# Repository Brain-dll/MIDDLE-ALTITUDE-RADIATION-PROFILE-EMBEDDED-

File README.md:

# Radiation-Profile-of-3000
Radiation profile of middle altitude rocket's route will be created at this project as payload mission

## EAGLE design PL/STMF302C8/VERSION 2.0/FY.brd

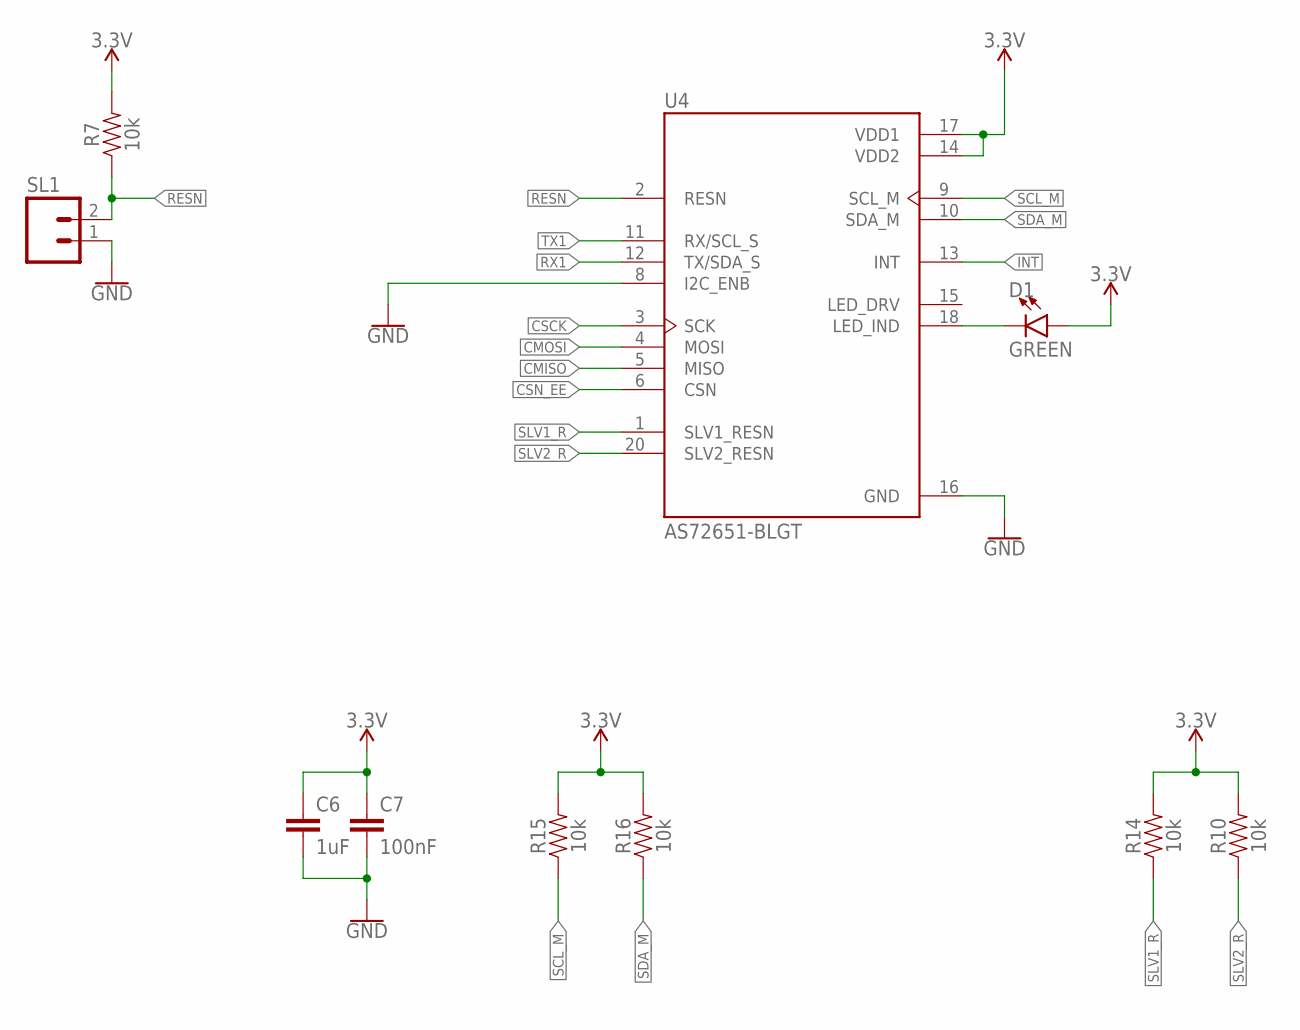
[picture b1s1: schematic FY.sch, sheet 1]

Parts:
C6: 1uF; 0603
C7: 100nF; 0603
D1: GREEN; LED-0603
R7, R10, R14, R15, R16: 10k; 0603
SL1: M02; 02P
U4: AS72651-BLGT; PQFN65P470X450X270-20N

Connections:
3.3V: C6.1, C7.1, D1.A, R7.2, R10.2, R14.2, R15.2, R16.2, U4.14 (VDD2), U4.17 (VDD1); also elsewhere on the board
CMISO: U4.5 (MISO); also elsewhere on the board
CMOSI: U4.4 (MOSI); also elsewhere on the board
CSCK: U4.3 (SCK); also elsewhere on the board
CSN_EE: U4.6 (CSN); also elsewhere on the board
GND: C6.2, C7.2, SL1.1, U4.8 (I2C_ENB), U4.16 (GND); also elsewhere on the board
INT: U4.13 (INT); also elsewhere on the board
unnamed: D1.C, U4.18 (LED_IND)
RESN: R7.1, SL1.2, U4.2 (RESN)
RX1: U4.12 (TX/SDA_S); also elsewhere on the board
SCL_M: R15.1, U4.9 (SCL_M); also elsewhere on the board
SDA_M: R16.1, U4.10 (SDA_M); also elsewhere on the board
SLV1_R: R14.1, U4.1 (SLV1_RESN); also elsewhere on the board
SLV2_R: R10.1, U4.20 (SLV2_RESN); also elsewhere on the board
TX1: U4.11 (RX/SCL_S); also elsewhere on the board

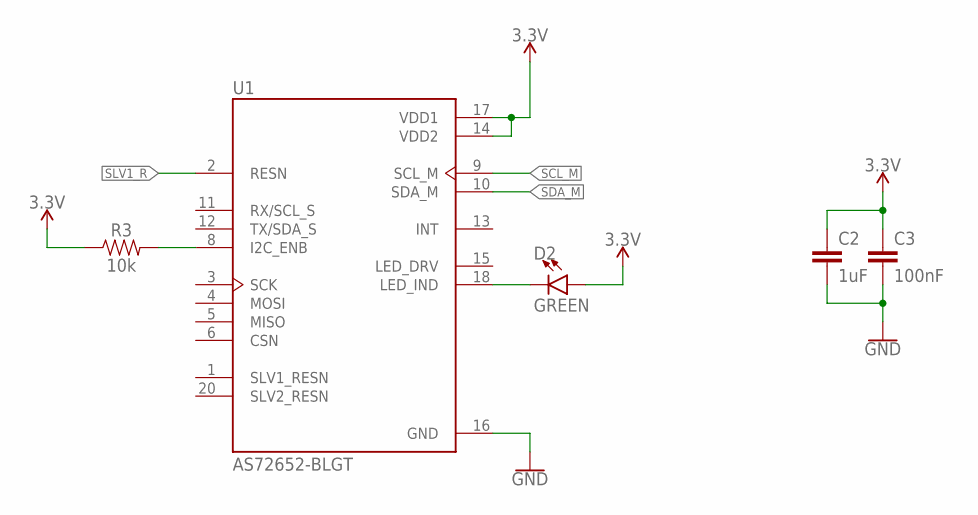
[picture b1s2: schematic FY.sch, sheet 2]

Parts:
C2: 1uF; 0603
C3: 100nF; 0603
D2: GREEN; LED-0603
R3: 10k; 0603
U1: AS72652-BLGT; PQFN65P470X450X270-20N

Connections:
3.3V: C2.1, C3.1, D2.A, R3.1, U1.14 (VDD2), U1.17 (VDD1); also elsewhere on the board
GND: C2.2, C3.2, U1.16 (GND); also elsewhere on the board
unnamed: R3.2, U1.8 (I2C_ENB)
unnamed: D2.C, U1.18 (LED_IND)
SCL_M: U1.9 (SCL_M); also elsewhere on the board
SDA_M: U1.10 (SDA_M); also elsewhere on the board
SLV1_R: U1.2 (RESN); also elsewhere on the board

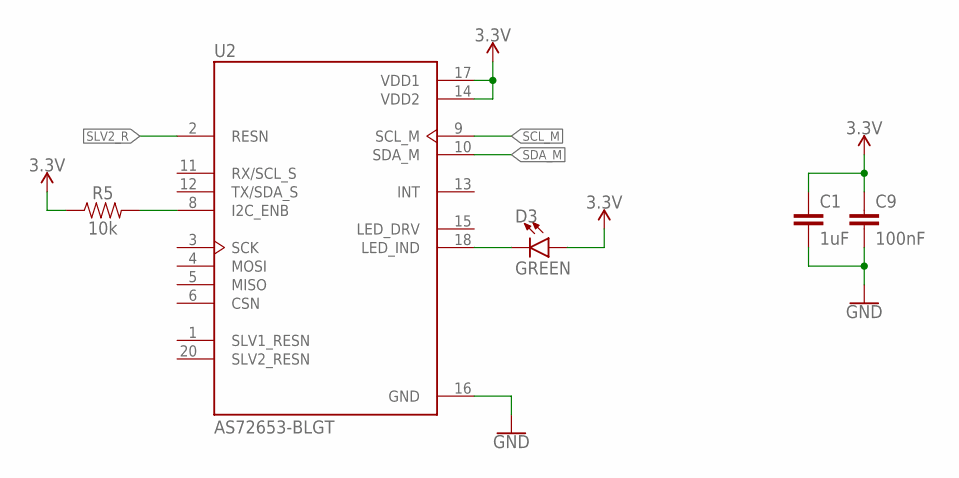
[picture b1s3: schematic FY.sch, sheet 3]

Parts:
C1: 1uF; 0603
C9: 100nF; 0603
D3: GREEN; LED-0603
R5: 10k; 0603
U2: AS72653-BLGT; PQFN65P470X450X270-20N

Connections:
3.3V: C1.1, C9.1, D3.A, R5.1, U2.14 (VDD2), U2.17 (VDD1); also elsewhere on the board
GND: C1.2, C9.2, U2.16 (GND); also elsewhere on the board
unnamed: D3.C, U2.18 (LED_IND)
unnamed: R5.2, U2.8 (I2C_ENB)
SCL_M: U2.9 (SCL_M); also elsewhere on the board
SDA_M: U2.10 (SDA_M); also elsewhere on the board
SLV2_R: U2.2 (RESN); also elsewhere on the board

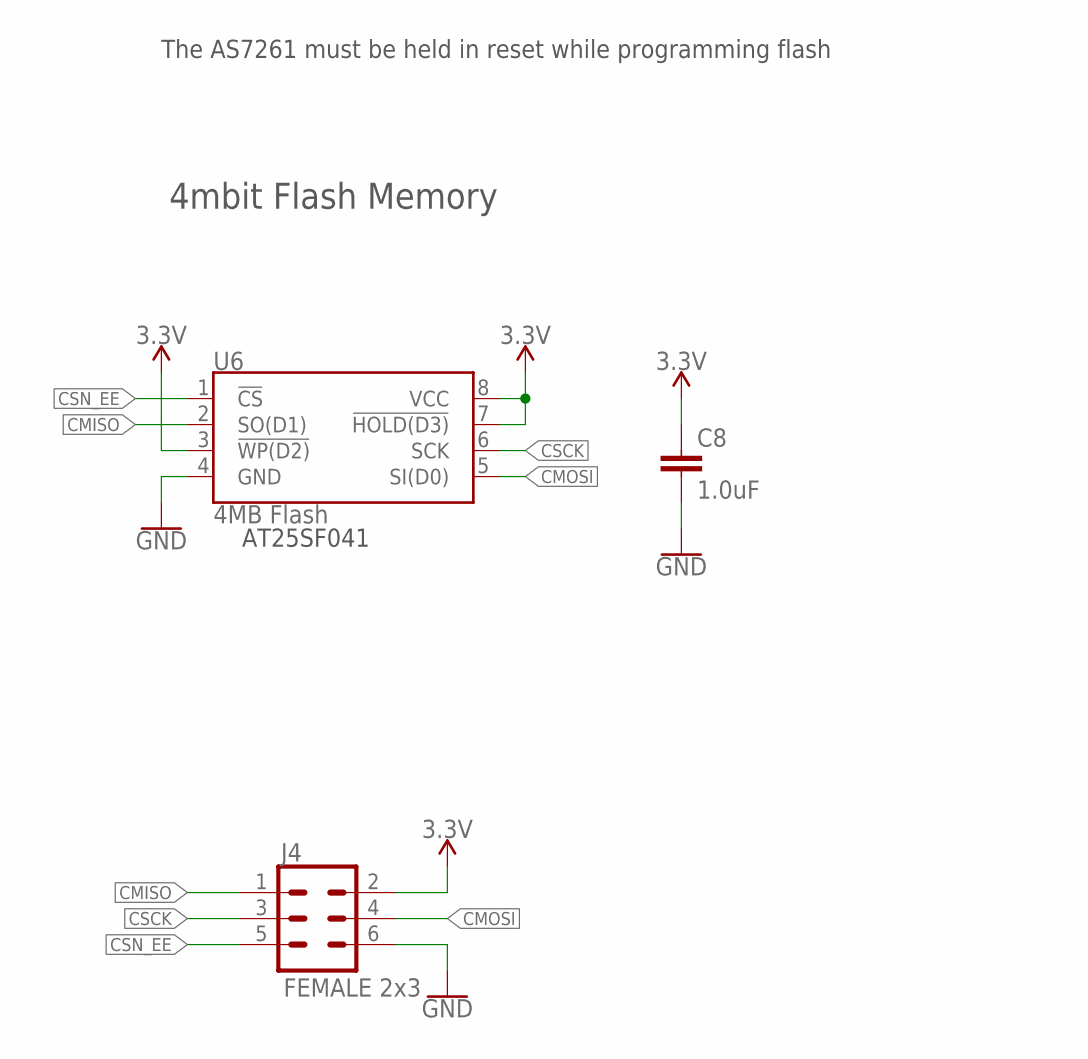
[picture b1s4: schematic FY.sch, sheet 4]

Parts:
C8: 1.0uF; 0603
J4: FEMALE 2x3; 2X3
U6: 4MB Flash; SO08

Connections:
3.3V: C8.1, J4.2, U6.3 (!WP(D2)), U6.7 (!HOLD(D3)), U6.8 (VCC); also elsewhere on the board
CMISO: J4.1, U6.2 (SO(D1)); also elsewhere on the board
CMOSI: J4.4, U6.5 (SI(D0)); also elsewhere on the board
CSCK: J4.3, U6.6 (SCK); also elsewhere on the board
CSN_EE: J4.5, U6.1 (!CS); also elsewhere on the board
GND: C8.2, J4.6, U6.4 (GND); also elsewhere on the board

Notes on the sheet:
4mbit Flash Memory
The AS7261 must be held in reset while programming flash
AT25SF041

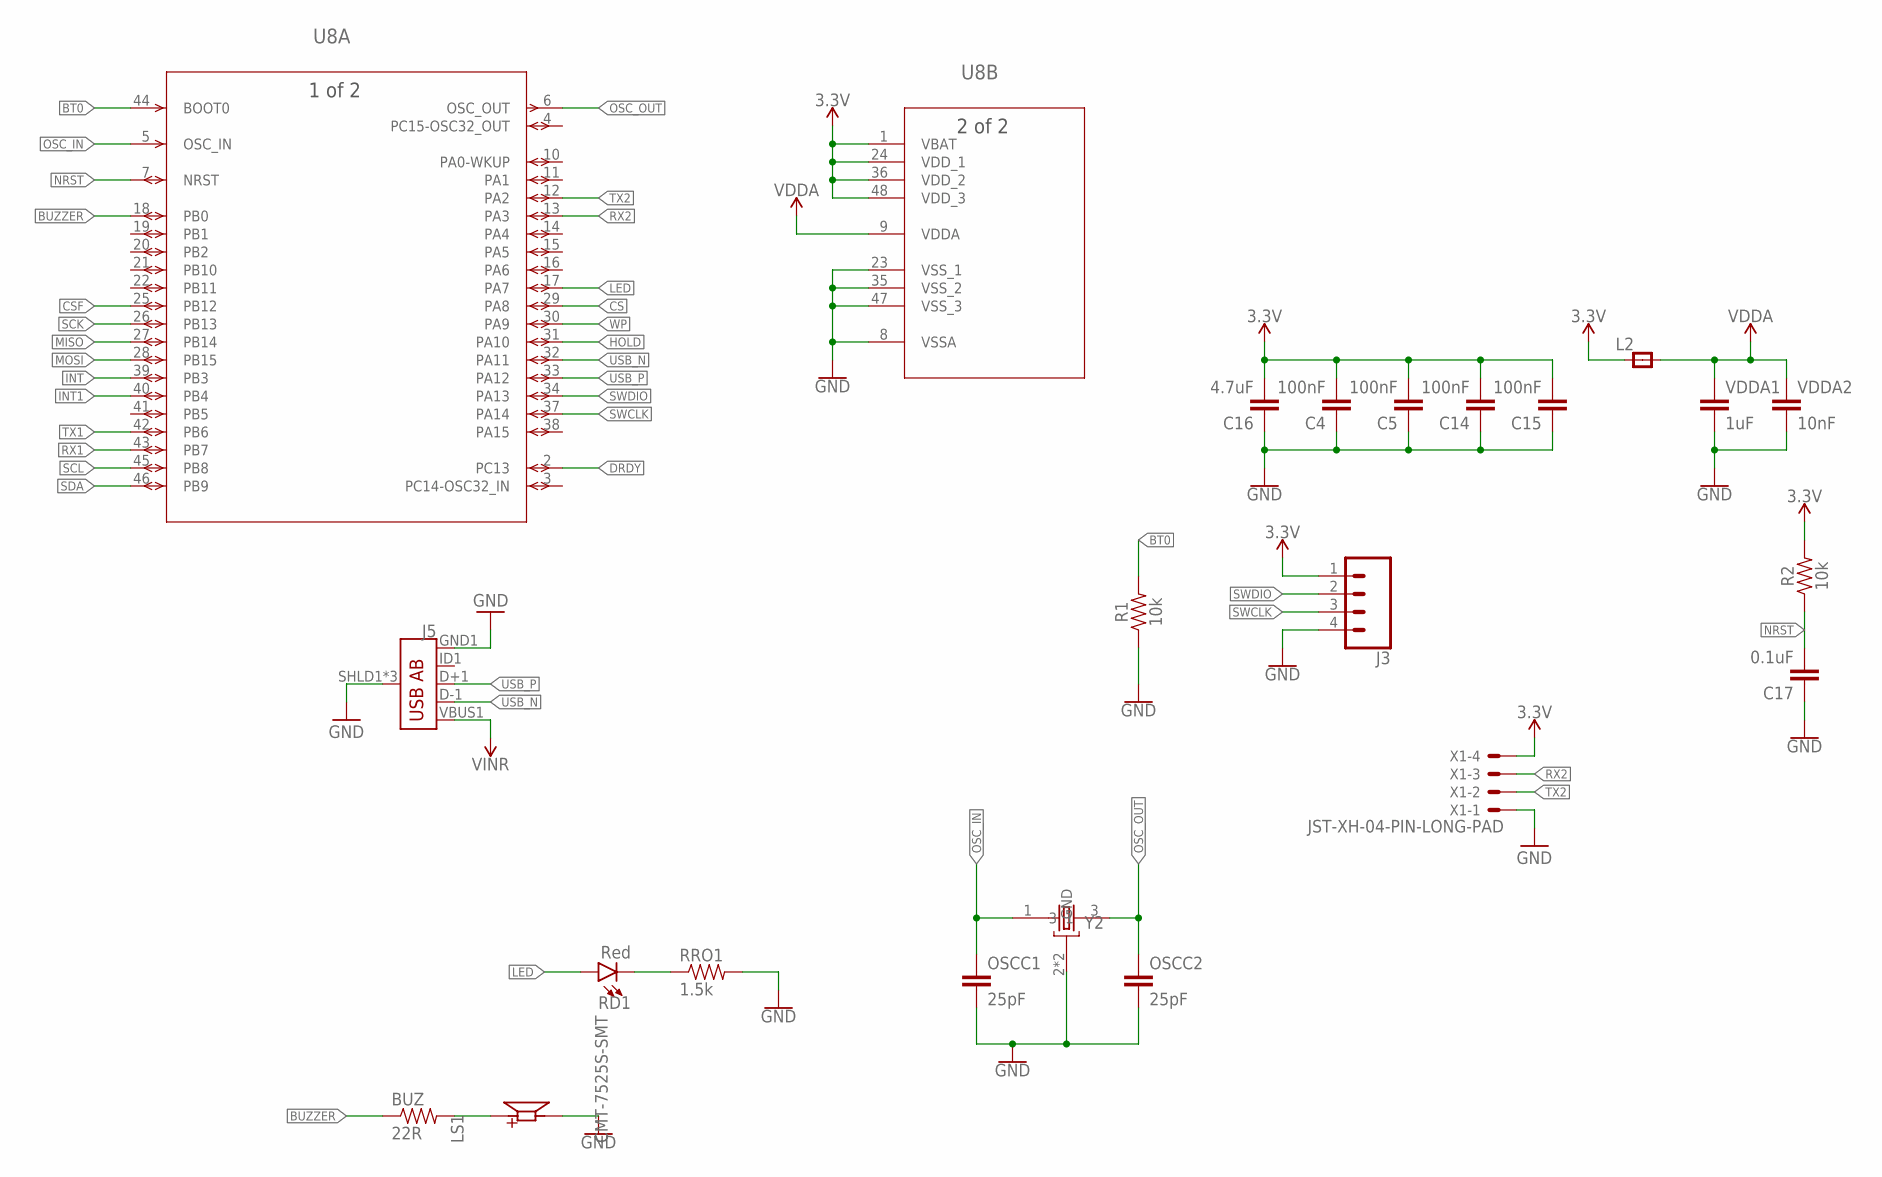
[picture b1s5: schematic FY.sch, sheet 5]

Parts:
BUZ: 22R; 0603-RES
C4, C5, C14, C15: 100nF; 0603
C16: 4.7uF; 0603
C17: 0.1uF; 0603
J3: CONN_04; 1X04
J5: USB_AB_SMT; USB-AB-MICRO-SMD
L2: RC-MASTER-SMD_FB_0805MP; RC-MASTER-SMD_L0805MP
LS1: CMT-7525S-SMT; CUI_CMT-7525S-SMT
OSCC1, OSCC2: 25pF; 0603
R1, R2: 10k; 0603
RD1: Red; LED-0603
RRO1: 1.5k; 0603-RES
U8: STM32F103C8T6; LQFP48-7X7MM
VDDA1: 1uF; 0603
VDDA2: 10nF; 0603
X1: JST-XH-04-PIN-LONG-PAD; JST-XH-04-PACKAGE-LONG-PAD
Y2: ABM2B-8.000MHZ-10-1-U-T; OSCCC500X320X110-4N

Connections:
3.3V: C4.2, C5.2, C14.2, C15.2, C16.2, J3.1, L2.1, R2.2, U8.1 (VBAT), U8.24 (VDD_1), U8.36 (VDD_2), U8.48 (VDD_3), X1.4; also elsewhere on the board
BT0: R1.2, U8.44 (BOOT0)
BUZZER: BUZ.1, U8.18 (PB0)
CS: U8.29 (PA8); also elsewhere on the board
CSF: U8.25 (PB12); also elsewhere on the board
DRDY: U8.2 (PC13); also elsewhere on the board
GND: C4.1, C5.1, C14.1, C15.1, C16.1, C17.1, J3.4, J5.GND1 (GND), J5.SHLD1 (SHIELD), J5.SHLD2 (SHIELD), J5.SHLD3 (SHIELD), LS1.N, OSCC1.2, OSCC2.2, R1.1, RRO1.2, U8.8 (VSSA), U8.23 (VSS_1), U8.35 (VSS_2), U8.47 (VSS_3), VDDA1.2, VDDA2.2, X1.1, Y2.2 (GND), Y2.4 (GND); also elsewhere on the board
HOLD: U8.31 (PA10); also elsewhere on the board
INT: U8.39 (PB3); also elsewhere on the board
INT1: U8.40 (PB4); also elsewhere on the board
LED: RD1.A, U8.17 (PA7)
MISO: U8.27 (PB14); also elsewhere on the board
MOSI: U8.28 (PB15); also elsewhere on the board
unnamed: RD1.C, RRO1.1
unnamed 29: BUZ.2, LS1.P; also elsewhere on the board
NRST: C17.2, R2.1, U8.7 (NRST)
OSC_IN: OSCC1.1, U8.5 (OSC_IN), Y2.1
OSC_OUT: OSCC2.1, U8.6 (OSC_OUT), Y2.3
RX1: U8.43 (PB7); also elsewhere on the board
RX2: U8.13 (PA3), X1.3
SCK: U8.26 (PB13); also elsewhere on the board
SCL: U8.45 (PB8); also elsewhere on the board
SDA: U8.46 (PB9); also elsewhere on the board
SWCLK: J3.3, U8.37 (PA14)
SWDIO: J3.2, U8.34 (PA13)
TX1: U8.42 (PB6); also elsewhere on the board
TX2: U8.12 (PA2), X1.2
USB_N: J5.D-1 (D-), U8.32 (PA11)
USB_P: J5.D+1 (D+), U8.33 (PA12)
VDDA: L2.2, U8.9 (VDDA), VDDA1.1, VDDA2.1
VIN: J5.VBUS1 (VBUS); also elsewhere on the board
WP: U8.30 (PA9); also elsewhere on the board

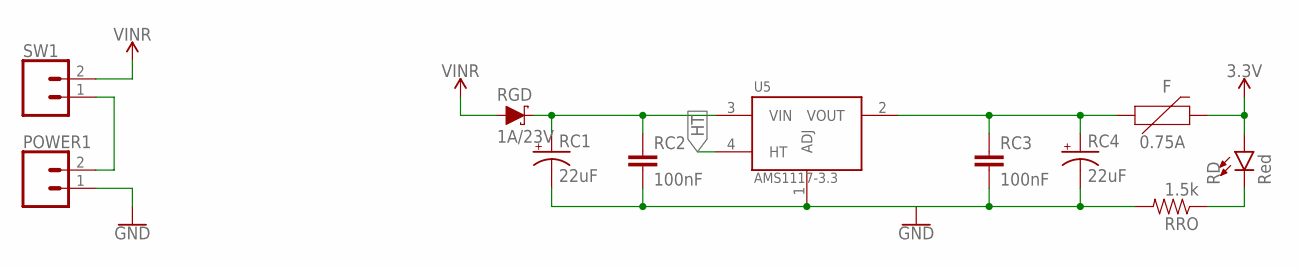
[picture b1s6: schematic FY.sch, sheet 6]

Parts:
F: 0.75A; 1206
POWER1: CONN_023.5MM-NO_SILK; SCREWTERMINAL-3.5MM-2-NS
RC1, RC4: 22uF; EIA3528
RC2, RC3: 100nF; 0603
RD: Red; LED-0603
RGD: 1A/23V; SOD-323
RRO: 1.5k; 0603-RES
SW1: CONN_023.5MM-NO_SILK; SCREWTERMINAL-3.5MM-2-NS
U5: AMS1117-3.3; SOT229P700X180-4N

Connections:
3.3V: F.2, RD.A; also elsewhere on the board
GND: POWER1.1, RC1.C (-), RC2.2, RC3.2, RC4.C (-), RRO.2, U5.1 (ADJ); also elsewhere on the board
HT: U5.4 (HT)
unnamed: POWER1.2, SW1.1
unnamed: F.1, RC3.1, RC4.A (+), U5.2 (VOUT)
unnamed: RD.C, RRO.1
VIN: RGD.A, SW1.2; also elsewhere on the board
VNR: RC1.A (+), RC2.1, RGD.C, U5.3 (VIN)

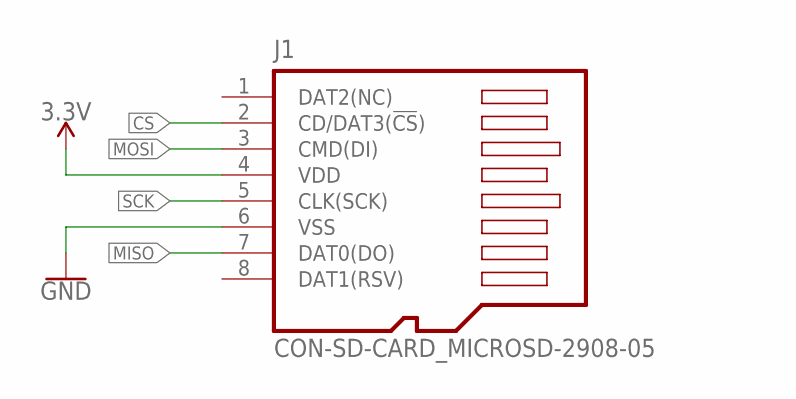
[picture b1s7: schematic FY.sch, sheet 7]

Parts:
J1: CON-SD-CARD_MICROSD-2908-05; CON-SD-CARD_2908-05

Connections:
3.3V: J1.4 (VDD); also elsewhere on the board
CS: J1.2 (CD/DAT3(!CS!)); also elsewhere on the board
GND: J1.6 (VSS); also elsewhere on the board
MISO: J1.7 (DAT0(DO)); also elsewhere on the board
MOSI: J1.3 (CMD(DI)); also elsewhere on the board
SCK: J1.5 (CLK(SCK)); also elsewhere on the board

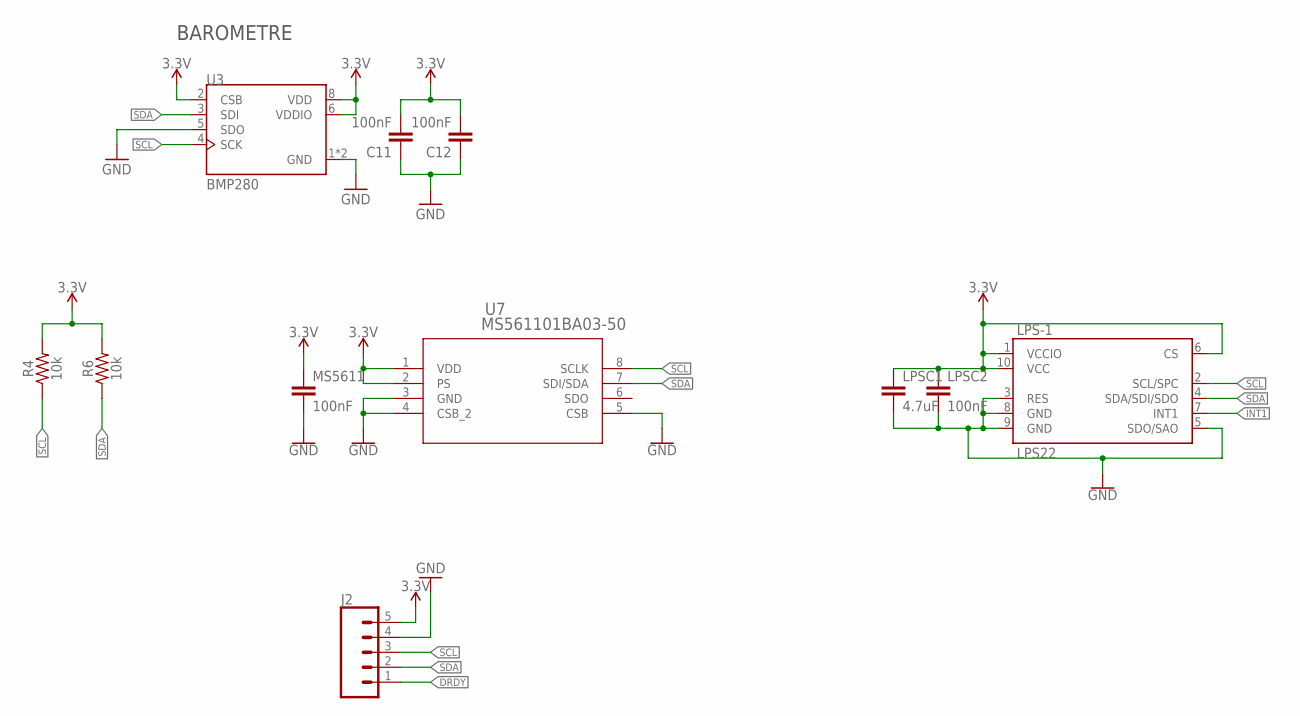
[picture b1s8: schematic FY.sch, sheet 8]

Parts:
C11, C12: 100nF; 0603
J2: CONN_05LOCK_LONGPADS; 1X05_LOCK_LONGPADS
LPS-1: LPS22; LPS22H
LPSC1: 4.7uF; 0603
LPSC2: 100nF; 0603
MS5611: 100nF; 0603
R4, R6: 10k; 0603
U3: BMP280; XDCR_BMP280
U7: MS561101BA03-50; SON8_MS5611_TEC

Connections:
3.3V: C11.2, C12.2, J2.5, LPS-1.1 (VCCIO), LPS-1.6 (CS), LPS-1.10 (VCC), LPSC1.1, LPSC2.1, MS5611.1, R4.2, R6.2, U3.2 (CSB), U3.6 (VDDIO), U3.8 (VDD), U7.1 (VDD), U7.2 (PS); also elsewhere on the board
DRDY: J2.1; also elsewhere on the board
GND: C11.1, C12.1, J2.4, LPS-1.3 (RES), LPS-1.5 (SDO/SAO), LPS-1.8 (GND), LPS-1.9 (GND), LPSC1.2, LPSC2.2, MS5611.2, U3.1 (GND), U3.5 (SDO), U3.7 (GND), U7.3 (GND), U7.4 (CSB_2), U7.5 (CSB); also elsewhere on the board
INT1: LPS-1.7 (INT1); also elsewhere on the board
SCL: J2.3, LPS-1.2 (SCL/SPC), R4.1, U3.4 (SCK), U7.8 (SCLK); also elsewhere on the board
SDA: J2.2, LPS-1.4 (SDA/SDI/SDO), R6.1, U3.3 (SDI), U7.7 (SDI/SDA); also elsewhere on the board

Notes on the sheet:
BAROMETRE

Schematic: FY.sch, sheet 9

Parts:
HOLDR: 10k; 0603-RES
IC1: EN25F40-100GCP-TR; SO08-SKINNYPADS
WPR: 10k; 0603-RES

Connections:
3.3V: HOLDR.2, IC1.8 (VDD); also elsewhere on the board
CSF: IC1.1 (R); also elsewhere on the board
GND: IC1.4 (GND), WPR.1; also elsewhere on the board
HOLD: HOLDR.1, IC1.7 (SET); also elsewhere on the board
MISO: IC1.2 (G); also elsewhere on the board
MOSI: IC1.5 (DO); also elsewhere on the board
SCK: IC1.6 (DIN); also elsewhere on the board
WP: IC1.3 (B), WPR.2; also elsewhere on the board

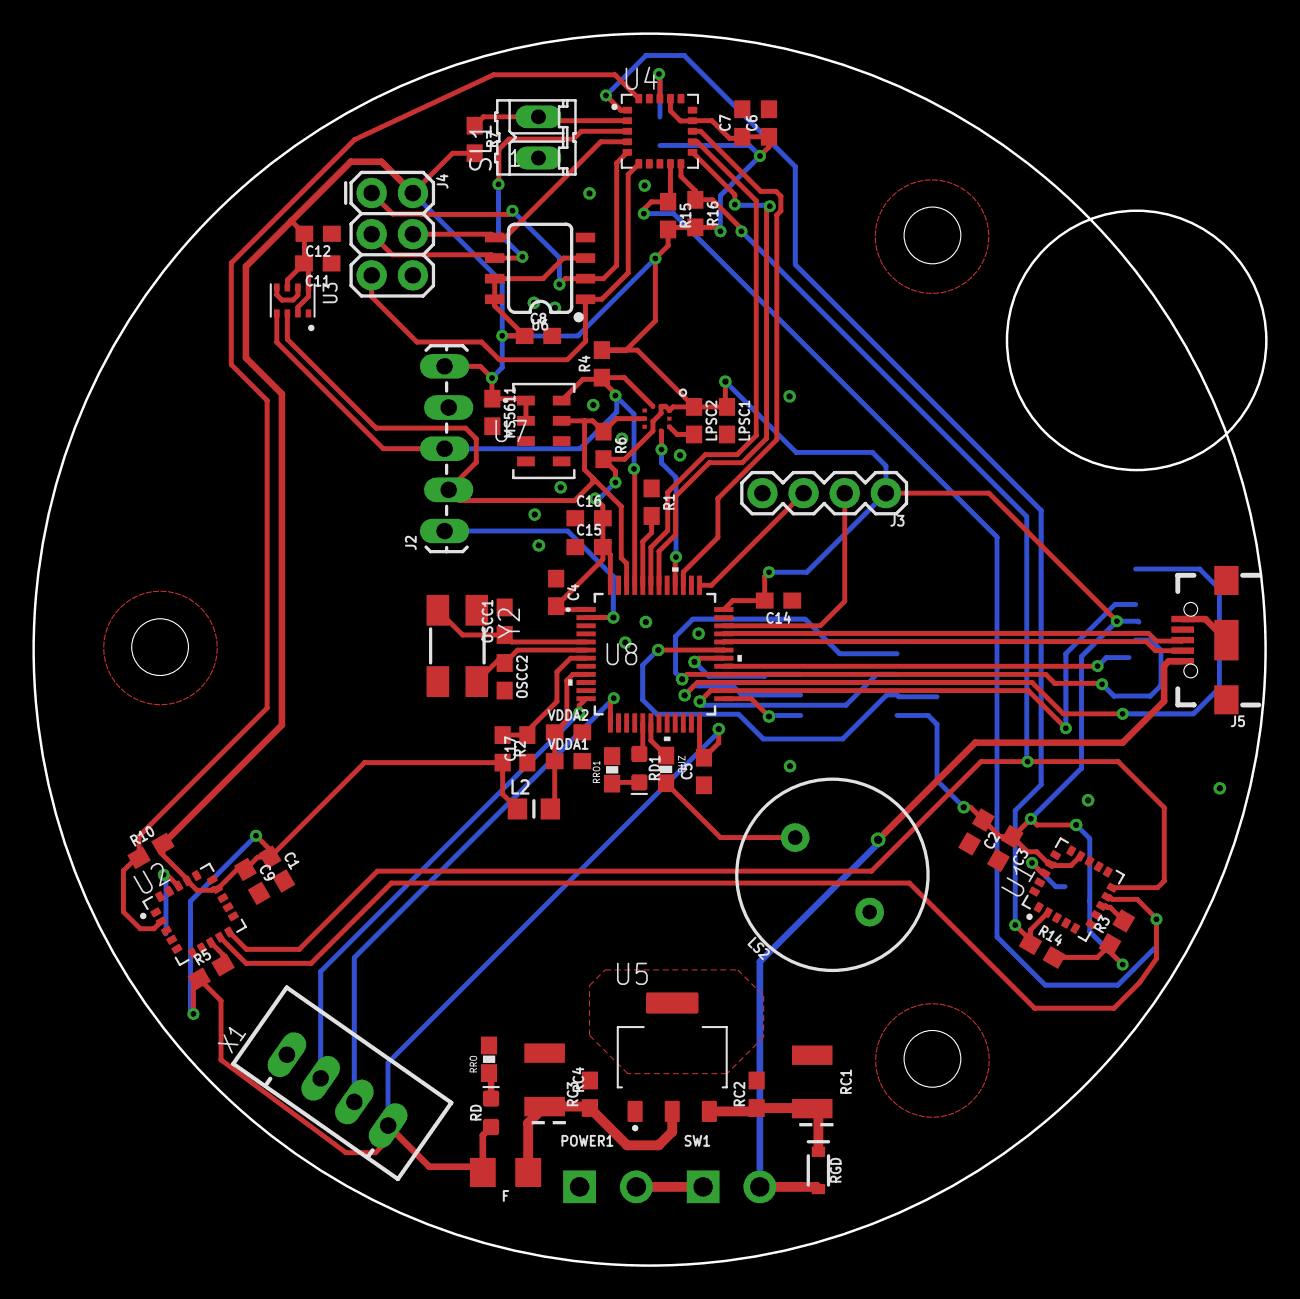
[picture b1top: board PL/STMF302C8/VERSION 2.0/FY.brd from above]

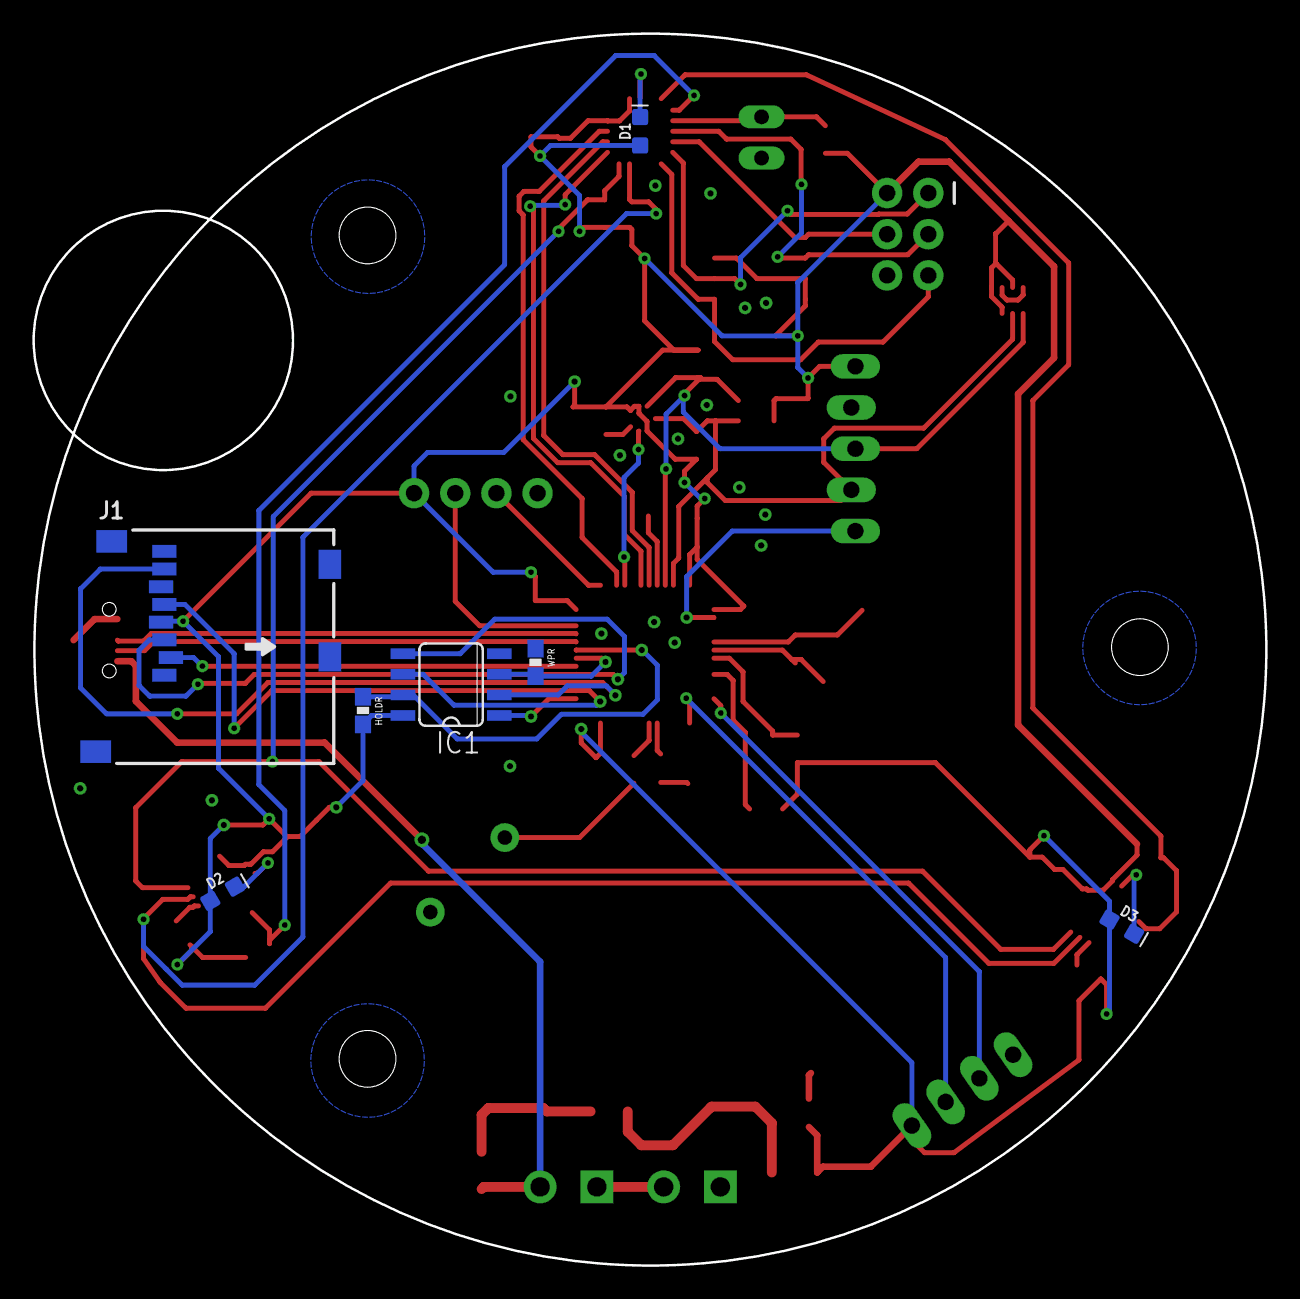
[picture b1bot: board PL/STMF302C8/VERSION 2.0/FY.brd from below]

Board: 2 copper layers, 76.0 x 76.0 mm, 71 parts (7 on the bottom side), 50 nets.

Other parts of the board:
LS2: BUZZER-PTH; BUZZER-12MM

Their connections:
GND: LS2.-; also elsewhere on the board
unnamed 29: LS2.+; also elsewhere on the board

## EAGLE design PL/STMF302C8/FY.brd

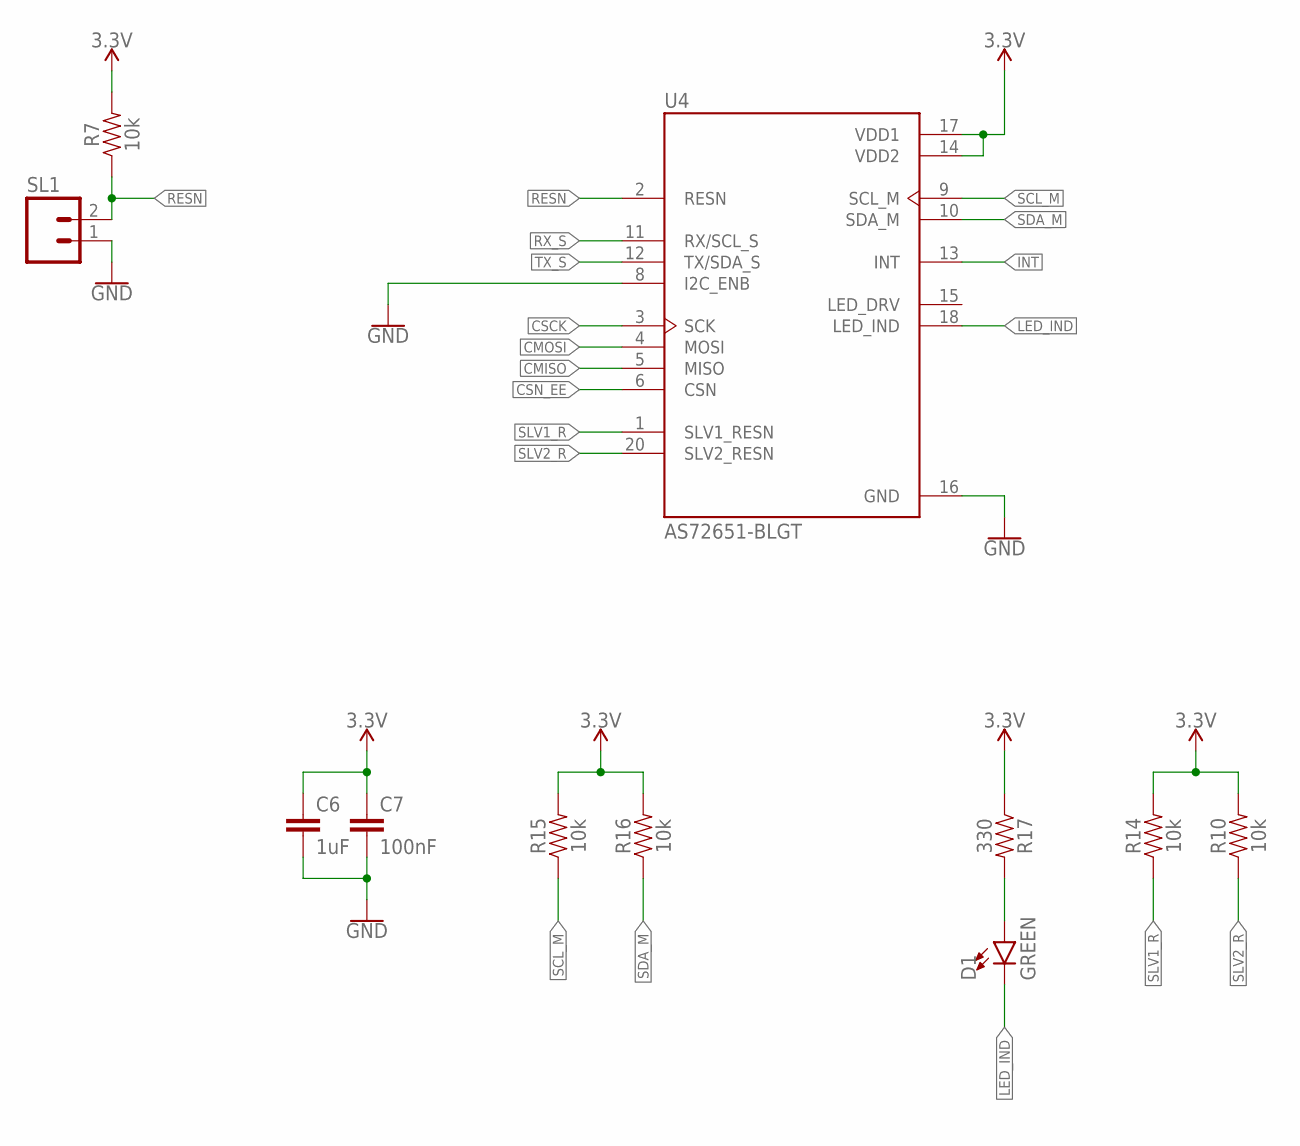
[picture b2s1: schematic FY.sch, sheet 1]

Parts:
C6: 1uF; 0603
C7: 100nF; 0603
D1: GREEN; LED-0603
R7, R10, R14, R15, R16: 10k; 0603
R17: 330; 0603
SL1: M02; 02P
U4: AS72651-BLGT; PQFN65P470X450X270-20N

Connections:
3.3V: C6.1, C7.1, R7.2, R10.2, R14.2, R15.2, R16.2, R17.1, U4.14 (VDD2), U4.17 (VDD1); also elsewhere on the board
CMISO: U4.5 (MISO); also elsewhere on the board
CMOSI: U4.4 (MOSI); also elsewhere on the board
CSCK: U4.3 (SCK); also elsewhere on the board
CSN_EE: U4.6 (CSN); also elsewhere on the board
GND: C6.2, C7.2, SL1.1, U4.8 (I2C_ENB), U4.16 (GND); also elsewhere on the board
INT: U4.13 (INT); also elsewhere on the board
LED_IND: D1.C, U4.18 (LED_IND)
unnamed: D1.A, R17.2
RESN: R7.1, SL1.2, U4.2 (RESN)
RX_S: U4.11 (RX/SCL_S); also elsewhere on the board
SCL_M: R15.1, U4.9 (SCL_M); also elsewhere on the board
SDA_M: R16.1, U4.10 (SDA_M); also elsewhere on the board
SLV1_R: R14.1, U4.1 (SLV1_RESN); also elsewhere on the board
SLV2_R: R10.1, U4.20 (SLV2_RESN); also elsewhere on the board
TX_S: U4.12 (TX/SDA_S); also elsewhere on the board

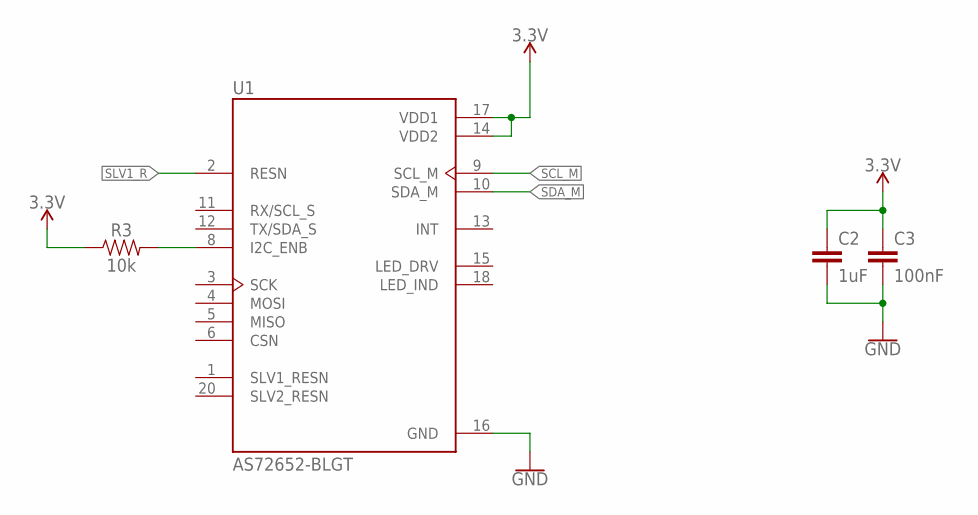
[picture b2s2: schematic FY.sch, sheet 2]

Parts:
C2: 1uF; 0603
C3: 100nF; 0603
R3: 10k; 0603
U1: AS72652-BLGT; PQFN65P470X450X270-20N

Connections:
3.3V: C2.1, C3.1, R3.1, U1.14 (VDD2), U1.17 (VDD1); also elsewhere on the board
GND: C2.2, C3.2, U1.16 (GND); also elsewhere on the board
unnamed: R3.2, U1.8 (I2C_ENB)
SCL_M: U1.9 (SCL_M); also elsewhere on the board
SDA_M: U1.10 (SDA_M); also elsewhere on the board
SLV1_R: U1.2 (RESN); also elsewhere on the board

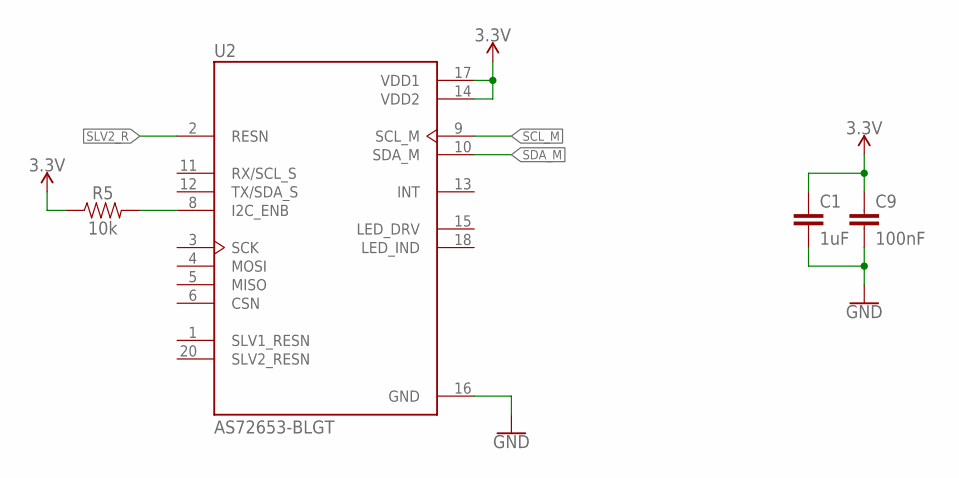
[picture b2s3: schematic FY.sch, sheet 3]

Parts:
C1: 1uF; 0603
C9: 100nF; 0603
R5: 10k; 0603
U2: AS72653-BLGT; PQFN65P470X450X270-20N

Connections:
3.3V: C1.1, C9.1, R5.1, U2.14 (VDD2), U2.17 (VDD1); also elsewhere on the board
GND: C1.2, C9.2, U2.16 (GND); also elsewhere on the board
unnamed: R5.2, U2.8 (I2C_ENB)
SCL_M: U2.9 (SCL_M); also elsewhere on the board
SDA_M: U2.10 (SDA_M); also elsewhere on the board
SLV2_R: U2.2 (RESN); also elsewhere on the board

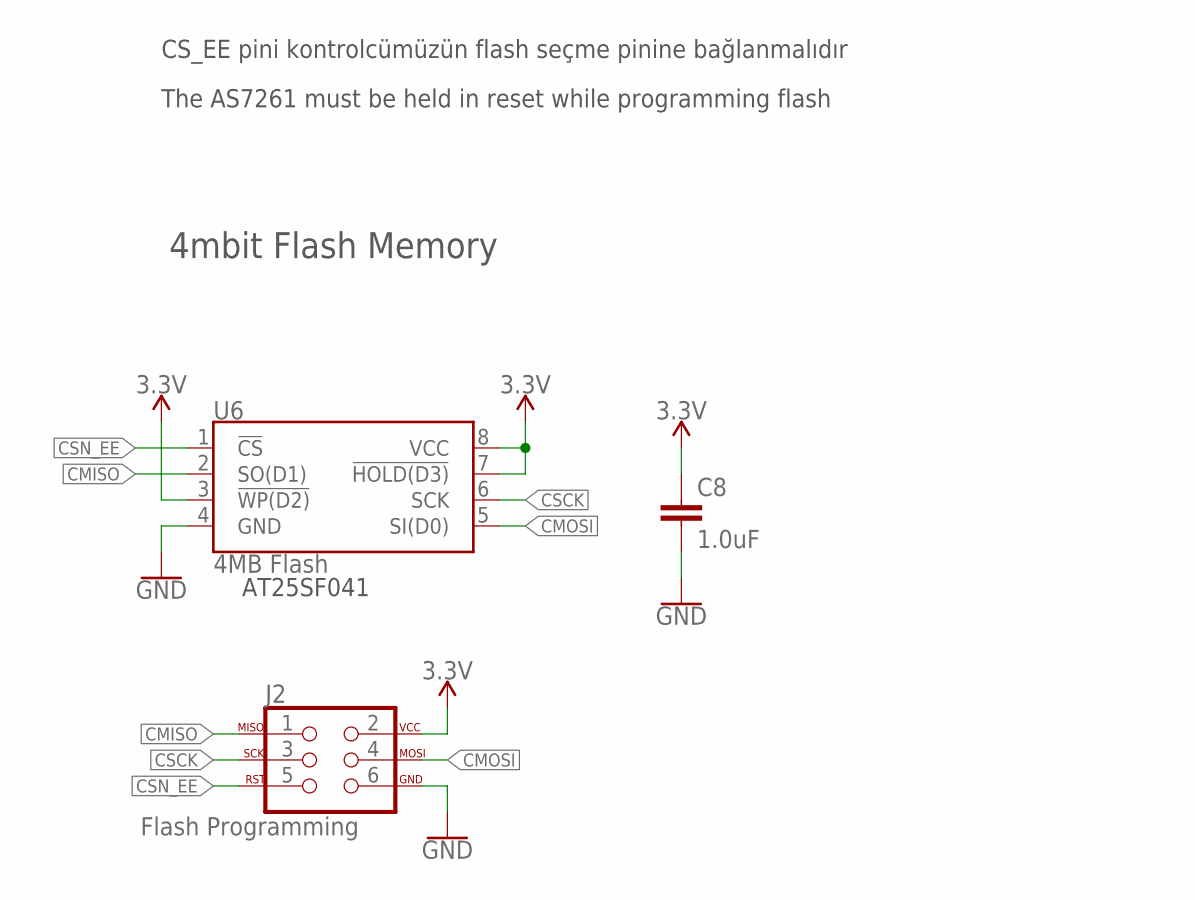
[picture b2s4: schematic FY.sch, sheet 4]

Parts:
C8: 1.0uF; 0603
J2: Flash Programming; 2X3_TEST_POINTS
U6: 4MB Flash; SO08

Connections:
3.3V: C8.1, J2.2, U6.3 (!WP(D2)), U6.7 (!HOLD(D3)), U6.8 (VCC); also elsewhere on the board
CMISO: J2.1, U6.2 (SO(D1)); also elsewhere on the board
CMOSI: J2.4, U6.5 (SI(D0)); also elsewhere on the board
CSCK: J2.3, U6.6 (SCK); also elsewhere on the board
CSN_EE: J2.5, U6.1 (!CS); also elsewhere on the board
GND: C8.2, J2.6, U6.4 (GND); also elsewhere on the board

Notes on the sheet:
4mbit Flash Memory
The AS7261 must be held in reset while programming flash
AT25SF041
CS_EE pini kontrolcümüzün flash seçme pinine bağlanmalıdır

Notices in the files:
parts and their libraries:
SparkFun-Capacitors: Licensing: Creative Commons ShareAlike 4.0 International - https://creativecommons.org/licenses/by-sa/4.0
COPYRIGHT: Copyright (C) 2018 Accelerated Designs. All rights reserved
Arduino-Sensors: Copyright (c) 2016-2017 Arduino LLC.  All right reserved.
